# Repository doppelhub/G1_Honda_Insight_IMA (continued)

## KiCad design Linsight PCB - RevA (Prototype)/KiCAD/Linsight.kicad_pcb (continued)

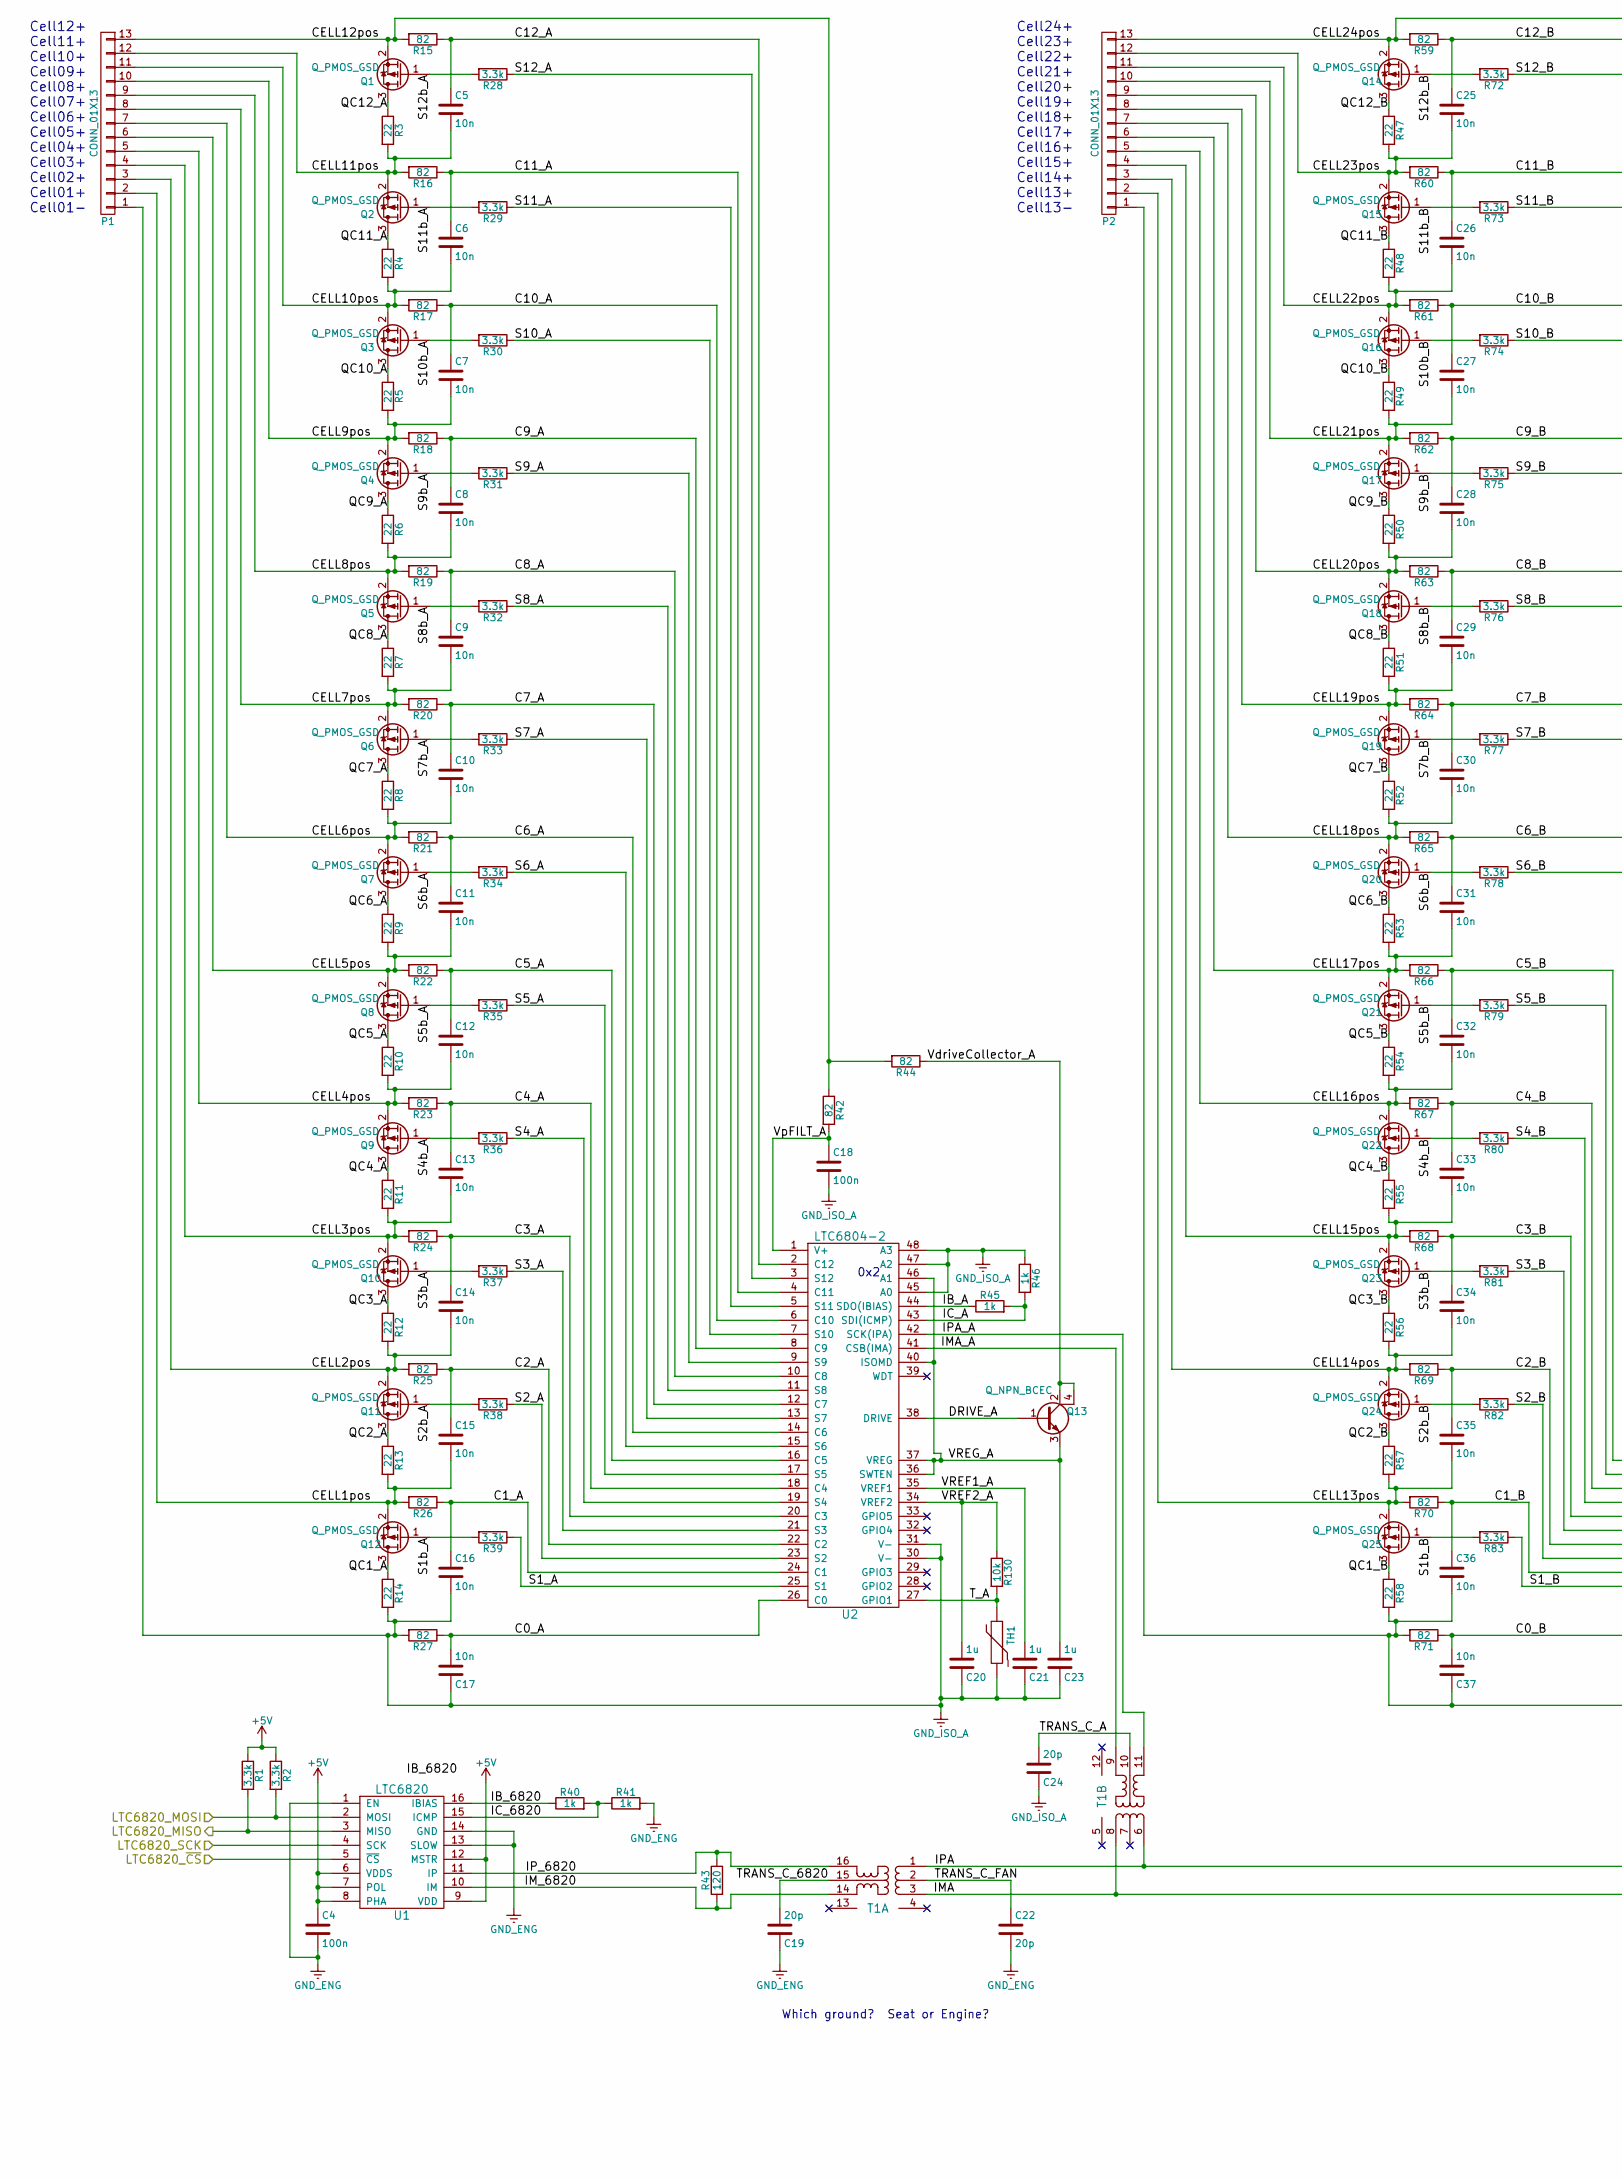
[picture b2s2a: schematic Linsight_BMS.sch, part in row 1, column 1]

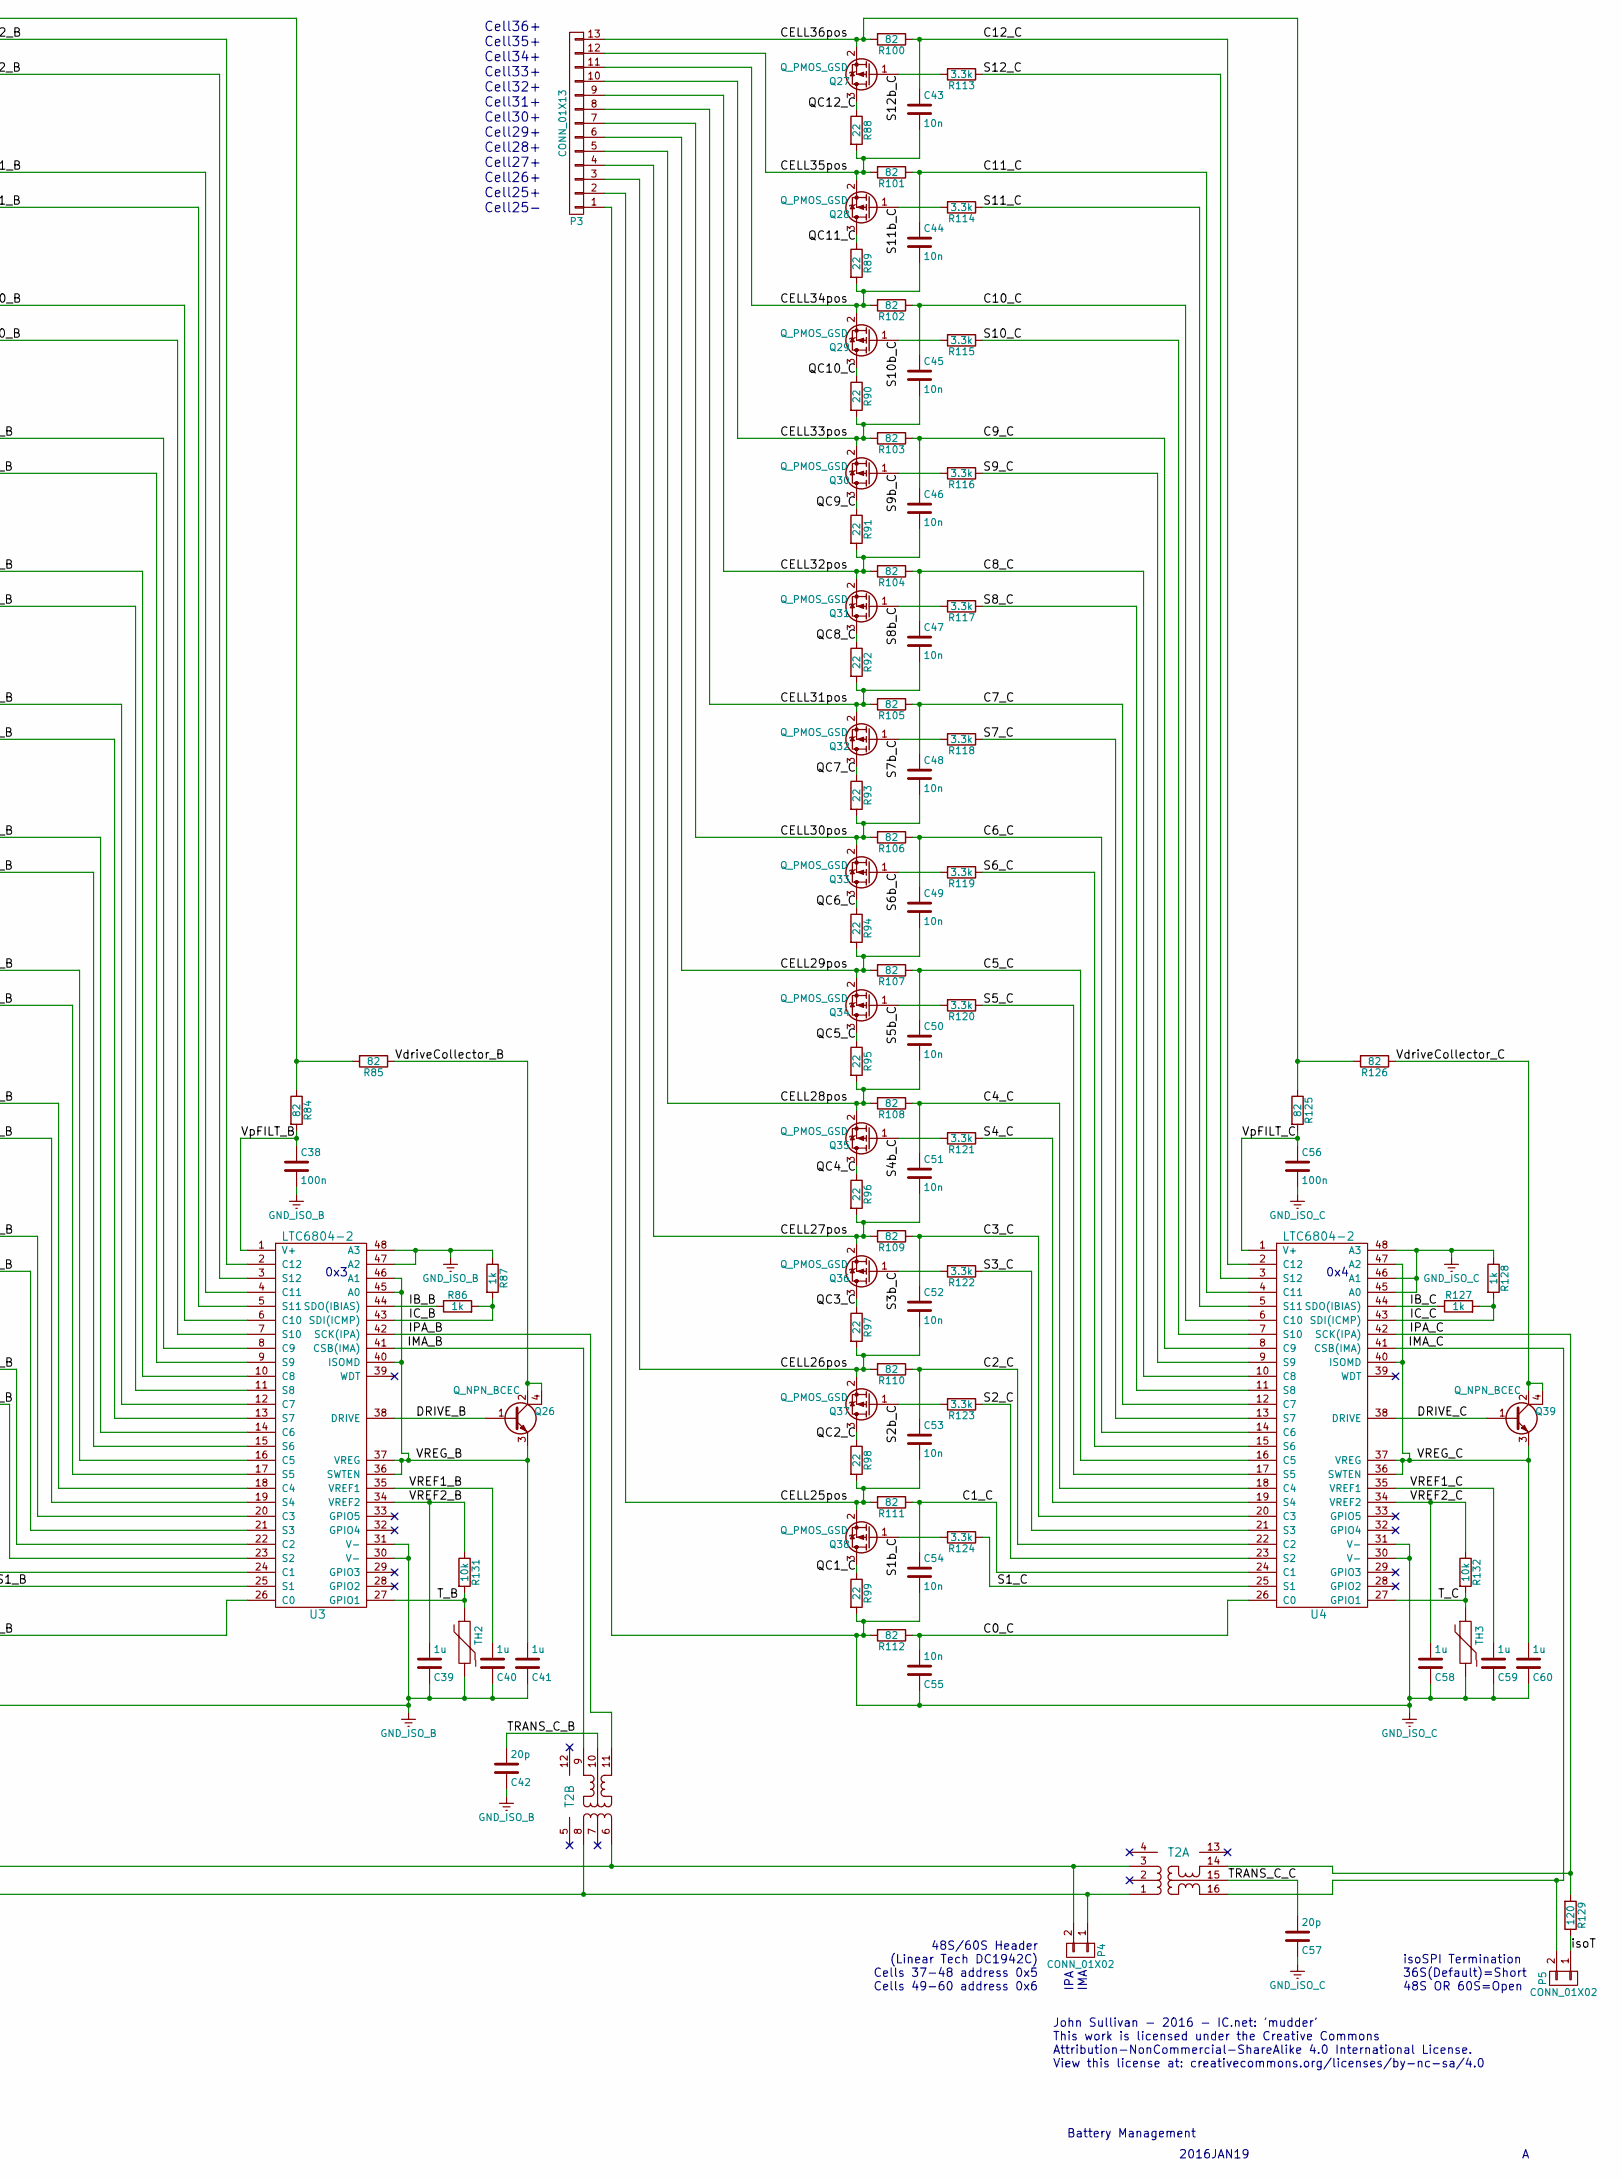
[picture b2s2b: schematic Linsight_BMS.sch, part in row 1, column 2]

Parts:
C4, C18, C38, C56: 100n; C_0805
C5, C6, C7, C8, C9, C10, C11, C12, C13, C14, C15, C16, C17, C25, C26, C27, C28, C29, C30, C31, C32, C33, C34, C35, C36, C37, C43, C44, C45, C46, C47, C48, C49, C50, C51, C52, C53, C54, C55: 10n; C_0805
C19, C22, C24, C42, C57: 20p; C_0805
C20, C21, C23, C39, C40, C41, C58, C59, C60: 1u; C_0805
P1, P2, P3: CONN_01X13; Conn_277-1232-ND
P4: CONN_01X02; Conn_1751248
P5: CONN_01X02; Pin_Header_Straight_1x02
Q1, Q2, Q3, Q4, Q5, Q6, Q7, Q8, Q9, Q10, Q11, Q12, Q14, Q15, Q16, Q17, Q18, Q19, Q20, Q21, Q22, Q23, Q24, Q25, Q27, Q28, Q29, Q30, Q31, Q32, Q33, Q34, Q35, Q36, Q37, Q38: Q_PMOS_GSD; SOT-23; Digikey BSS308PE-H6327TR-ND
Q13, Q26, Q39: Q_NPN_BCEC; SOT-223; Digikey BCP56-16T1GOSTR-ND
R1, R2, R28, R29, R30, R31, R32, R33, R34, R35, R36, R37, R38, R39, R72, R73, R74, R75, R76, R77, R78, R79, R80, R81, R82, R83, R113, R114, R115, R116, R117, R118, R119, R120, R121, R122, R123, R124: 3.3k; R_0805
R3, R4, R5, R6, R7, R8, R9, R10, R11, R12, R13, R14, R47, R48, R49, R50, R51, R52, R53, R54, R55, R56, R57, R58, R88, R89, R90, R91, R92, R93, R94, R95, R96, R97, R98, R99: 22; R_2512
R15, R16, R17, R18, R19, R20, R21, R22, R23, R24, R25, R26, R27, R42, R44, R59, R60, R61, R62, R63, R64, R65, R66, R67, R68, R69, R70, R71, R84, R85, R100, R101, R102, R103, R104, R105, R106, R107, R108, R109, R110, R111, R112, R125, R126: 82; R_0805
R40, R41, R45, R46, R86, R87, R127, R128: 1k; R_0805
R43, R129: 120; R_0805
R130, R131, R132: 10k; R_0805
T1, T2: Trans_7490100111; Trans_7490100111A
TH1, TH2, TH3: THERMISTOR; R_0805
U1: LTC6820; LTC6820_MSOP
U2, U3, U4: LTC6804-2

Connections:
+5V: C4.1, R1.1, R2.1, U1.6 (VDDS), U1.7 (POL), U1.8 (PHA), U1.9 (VDD), U1.12 (MSTR); also elsewhere on the board
/Linsight BMS/C0_A: C17.2, R27.1, U2.26 (C0)
/Linsight BMS/C0_B: C37.2, R71.1, U3.26 (C0)
/Linsight BMS/C0_C: C55.2, R112.1, U4.26 (C0)
/Linsight BMS/C1_A: C16.1, R26.1, U2.24 (C1)
/Linsight BMS/C1_B: C36.1, R70.1, U3.24 (C1)
/Linsight BMS/C1_C: C54.1, R111.1, U4.24 (C1)
/Linsight BMS/C2_A: C15.1, R25.1, U2.22 (C2)
/Linsight BMS/C2_B: C35.1, R69.1, U3.22 (C2)
/Linsight BMS/C2_C: C53.1, R110.1, U4.22 (C2)
/Linsight BMS/C3_A: C14.1, R24.1, U2.20 (C3)
/Linsight BMS/C3_B: C34.1, R68.1, U3.20 (C3)
/Linsight BMS/C3_C: C52.1, R109.1, U4.20 (C3)
/Linsight BMS/C4_A: C13.1, R23.1, U2.18 (C4)
/Linsight BMS/C4_B: C33.1, R67.1, U3.18 (C4)
/Linsight BMS/C4_C: C51.1, R108.1, U4.18 (C4)
/Linsight BMS/C5_A: C12.1, R22.1, U2.16 (C5)
/Linsight BMS/C5_B: C32.1, R66.1, U3.16 (C5)
/Linsight BMS/C5_C: C50.1, R107.1, U4.16 (C5)
/Linsight BMS/C6_A: C11.1, R21.1, U2.14 (C6)
/Linsight BMS/C6_B: C31.1, R65.1, U3.14 (C6)
/Linsight BMS/C6_C: C49.1, R106.1, U4.14 (C6)
/Linsight BMS/C7_A: C10.1, R20.1, U2.12 (C7)
/Linsight BMS/C7_B: C30.1, R64.1, U3.12 (C7)
/Linsight BMS/C7_C: C48.1, R105.1, U4.12 (C7)
/Linsight BMS/C8_A: C9.1, R19.1, U2.10 (C8)
/Linsight BMS/C8_B: C29.1, R63.1, U3.10 (C8)
/Linsight BMS/C8_C: C47.1, R104.1, U4.10 (C8)
/Linsight BMS/C9_A: C8.1, R18.1, U2.8 (C9)
/Linsight BMS/C9_B: C28.1, R62.1, U3.8 (C9)
/Linsight BMS/C9_C: C46.1, R103.1, U4.8 (C9)
/Linsight BMS/C10_A: C7.1, R17.1, U2.6 (C10)
/Linsight BMS/C10_B: C27.1, R61.1, U3.6 (C10)
/Linsight BMS/C10_C: C45.1, R102.1, U4.6 (C10)
/Linsight BMS/C11_A: C6.1, R16.1, U2.4 (C11)
/Linsight BMS/C11_B: C26.1, R60.1, U3.4 (C11)
/Linsight BMS/C11_C: C44.1, R101.1, U4.4 (C11)
/Linsight BMS/C12_A: C5.1, R15.1, U2.2 (C12)
/Linsight BMS/C12_B: C25.1, R59.1, U3.2 (C12)
/Linsight BMS/C12_C: C43.1, R100.1, U4.2 (C12)
/Linsight BMS/CELL1pos: C15.2, P1.2, Q12.2 (S), R13.2, R26.2
/Linsight BMS/CELL2pos: C14.2, P1.3, Q11.2 (S), R12.2, R25.2
/Linsight BMS/CELL3pos: C13.2, P1.4, Q10.2 (S), R11.2, R24.2
/Linsight BMS/CELL4pos: C12.2, P1.5, Q9.2 (S), R10.2, R23.2
/Linsight BMS/CELL5pos: C11.2, P1.6, Q8.2 (S), R9.2, R22.2
/Linsight BMS/CELL6pos: C10.2, P1.7, Q7.2 (S), R8.2, R21.2
/Linsight BMS/CELL7pos: C9.2, P1.8, Q6.2 (S), R7.2, R20.2
/Linsight BMS/CELL8pos: C8.2, P1.9, Q5.2 (S), R6.2, R19.2
/Linsight BMS/CELL9pos: C7.2, P1.10, Q4.2 (S), R5.2, R18.2
/Linsight BMS/CELL10pos: C6.2, P1.11, Q3.2 (S), R4.2, R17.2
/Linsight BMS/CELL11pos: C5.2, P1.12, Q2.2 (S), R3.2, R16.2
/Linsight BMS/CELL12pos: P1.13, Q1.2 (S), R15.2, R42.1, R44.2
/Linsight BMS/CELL13pos: C35.2, P2.2, Q25.2 (S), R57.2, R70.2
/Linsight BMS/CELL14pos: C34.2, P2.3, Q24.2 (S), R56.2, R69.2
/Linsight BMS/CELL15pos: C33.2, P2.4, Q23.2 (S), R55.2, R68.2
/Linsight BMS/CELL16pos: C32.2, P2.5, Q22.2 (S), R54.2, R67.2
/Linsight BMS/CELL17pos: C31.2, P2.6, Q21.2 (S), R53.2, R66.2
/Linsight BMS/CELL18pos: C30.2, P2.7, Q20.2 (S), R52.2, R65.2
/Linsight BMS/CELL19pos: C29.2, P2.8, Q19.2 (S), R51.2, R64.2
/Linsight BMS/CELL20pos: C28.2, P2.9, Q18.2 (S), R50.2, R63.2
/Linsight BMS/CELL21pos: C27.2, P2.10, Q17.2 (S), R49.2, R62.2
/Linsight BMS/CELL22pos: C26.2, P2.11, Q16.2 (S), R48.2, R61.2
/Linsight BMS/CELL23pos: C25.2, P2.12, Q15.2 (S), R47.2, R60.2
/Linsight BMS/CELL24pos: P2.13, Q14.2 (S), R59.2, R84.1, R85.2
/Linsight BMS/CELL25pos: C53.2, P3.2, Q38.2 (S), R98.2, R111.2
/Linsight BMS/CELL26pos: C52.2, P3.3, Q37.2 (S), R97.2, R110.2
/Linsight BMS/CELL27pos: C51.2, P3.4, Q36.2 (S), R96.2, R109.2
/Linsight BMS/CELL28pos: C50.2, P3.5, Q35.2 (S), R95.2, R108.2
/Linsight BMS/CELL29pos: C49.2, P3.6, Q34.2 (S), R94.2, R107.2
/Linsight BMS/CELL30pos: C48.2, P3.7, Q33.2 (S), R93.2, R106.2
/Linsight BMS/CELL31pos: C47.2, P3.8, Q32.2 (S), R92.2, R105.2
/Linsight BMS/CELL32pos: C46.2, P3.9, Q31.2 (S), R91.2, R104.2
/Linsight BMS/CELL33pos: C45.2, P3.10, Q30.2 (S), R90.2, R103.2
/Linsight BMS/CELL34pos: C44.2, P3.11, Q29.2 (S), R89.2, R102.2
/Linsight BMS/CELL35pos: C43.2, P3.12, Q28.2 (S), R88.2, R101.2
/Linsight BMS/CELL36pos: P3.13, Q27.2 (S), R100.2, R125.1, R126.2
/Linsight BMS/DRIVE_A: Q13.1 (B), U2.38 (DRIVE)
/Linsight BMS/DRIVE_B: Q26.1 (B), U3.38 (DRIVE)
/Linsight BMS/DRIVE_C: Q39.1 (B), U4.38 (DRIVE)
/Linsight BMS/IB_6820: R40.1, U1.16 (IBIAS)
/Linsight BMS/IB_A: R45.1, U2.44 (SDO(IBIAS))
/Linsight BMS/IB_B: R86.1, U3.44 (SDO(IBIAS))
/Linsight BMS/IB_C: R127.1, U4.44 (SDO(IBIAS))
/Linsight BMS/IC_6820: R40.2, R41.1, U1.15 (ICMP)
/Linsight BMS/IC_A: R45.2, R46.2, U2.43 (SDI(ICMP))
/Linsight BMS/IC_B: R86.2, R87.2, U3.43 (SDI(ICMP))
/Linsight BMS/IC_C: R127.2, R128.2, U4.43 (SDI(ICMP))
/Linsight BMS/IMA: P4.1, T1.3, T1.8, T2.1, T2.8
/Linsight BMS/IMA_A: T1.9, U2.41 (CSB(IMA))
/Linsight BMS/IMA_B: T2.9, U3.41 (CSB(IMA))
/Linsight BMS/IMA_C: P5.2, T2.16, U4.41 (CSB(IMA))
/Linsight BMS/IM_6820: R43.2, T1.14, U1.10 (IM)
/Linsight BMS/IPA: P4.2, T1.1, T1.6, T2.3, T2.6
/Linsight BMS/IPA_A: T1.11, U2.42 (SCK(IPA))
/Linsight BMS/IPA_B: T2.11, U3.42 (SCK(IPA))
/Linsight BMS/IPA_C: R129.2, T2.14, U4.42 (SCK(IPA))
/Linsight BMS/IP_6820: R43.1, T1.16, U1.11 (IP)
/Linsight BMS/LTC6820_MISO: R1.2, U1.3 (MISO); also elsewhere on the board
/Linsight BMS/LTC6820_MOSI: R2.2, U1.2 (MOSI); also elsewhere on the board
/Linsight BMS/LTC6820_SCK: U1.4 (SCK); also elsewhere on the board
/Linsight BMS/LTC6820_~CS: U1.5 (~CS); also elsewhere on the board
/Linsight BMS/QC1_A: Q12.3 (D), R14.1
/Linsight BMS/QC1_B: Q25.3 (D), R58.1
/Linsight BMS/QC1_C: Q38.3 (D), R99.1
/Linsight BMS/QC2_A: Q11.3 (D), R13.1
/Linsight BMS/QC2_B: Q24.3 (D), R57.1
/Linsight BMS/QC2_C: Q37.3 (D), R98.1
/Linsight BMS/QC3_A: Q10.3 (D), R12.1
/Linsight BMS/QC3_B: Q23.3 (D), R56.1
/Linsight BMS/QC3_C: Q36.3 (D), R97.1
/Linsight BMS/QC4_A: Q9.3 (D), R11.1
/Linsight BMS/QC4_B: Q22.3 (D), R55.1
/Linsight BMS/QC4_C: Q35.3 (D), R96.1
/Linsight BMS/QC5_A: Q8.3 (D), R10.1
/Linsight BMS/QC5_B: Q21.3 (D), R54.1
/Linsight BMS/QC5_C: Q34.3 (D), R95.1
/Linsight BMS/QC6_A: Q7.3 (D), R9.1
/Linsight BMS/QC6_B: Q20.3 (D), R53.1
/Linsight BMS/QC6_C: Q33.3 (D), R94.1
/Linsight BMS/QC7_A: Q6.3 (D), R8.1
/Linsight BMS/QC7_B: Q19.3 (D), R52.1
/Linsight BMS/QC7_C: Q32.3 (D), R93.1
/Linsight BMS/QC8_A: Q5.3 (D), R7.1
/Linsight BMS/QC8_B: Q18.3 (D), R51.1
/Linsight BMS/QC8_C: Q31.3 (D), R92.1
/Linsight BMS/QC9_A: Q4.3 (D), R6.1
/Linsight BMS/QC9_B: Q17.3 (D), R50.1
/Linsight BMS/QC9_C: Q30.3 (D), R91.1
/Linsight BMS/QC10_A: Q3.3 (D), R5.1
/Linsight BMS/QC10_B: Q16.3 (D), R49.1
/Linsight BMS/QC10_C: Q29.3 (D), R90.1
/Linsight BMS/QC11_A: Q2.3 (D), R4.1
/Linsight BMS/QC11_B: Q15.3 (D), R48.1
/Linsight BMS/QC11_C: Q28.3 (D), R89.1
/Linsight BMS/QC12_A: Q1.3 (D), R3.1
/Linsight BMS/QC12_B: Q14.3 (D), R47.1
/Linsight BMS/QC12_C: Q27.3 (D), R88.1
/Linsight BMS/S1_A: R39.1, U2.25 (S1)
/Linsight BMS/S1_B: R83.1, U3.25 (S1)
/Linsight BMS/S1_C: R124.1, U4.25 (S1)
/Linsight BMS/S1b_A: Q12.1 (G), R39.2
/Linsight BMS/S1b_B: Q25.1 (G), R83.2
/Linsight BMS/S1b_C: Q38.1 (G), R124.2
/Linsight BMS/S2_A: R38.1, U2.23 (S2)
/Linsight BMS/S2_B: R82.1, U3.23 (S2)
/Linsight BMS/S2_C: R123.1, U4.23 (S2)
/Linsight BMS/S2b_A: Q11.1 (G), R38.2
/Linsight BMS/S2b_B: Q24.1 (G), R82.2
/Linsight BMS/S2b_C: Q37.1 (G), R123.2
/Linsight BMS/S3_A: R37.1, U2.21 (S3)
/Linsight BMS/S3_B: R81.1, U3.21 (S3)
/Linsight BMS/S3_C: R122.1, U4.21 (S3)
/Linsight BMS/S3b_A: Q10.1 (G), R37.2
/Linsight BMS/S3b_B: Q23.1 (G), R81.2
/Linsight BMS/S3b_C: Q36.1 (G), R122.2
/Linsight BMS/S4_A: R36.1, U2.19 (S4)
/Linsight BMS/S4_B: R80.1, U3.19 (S4)
/Linsight BMS/S4_C: R121.1, U4.19 (S4)
/Linsight BMS/S4b_A: Q9.1 (G), R36.2
/Linsight BMS/S4b_B: Q22.1 (G), R80.2
/Linsight BMS/S4b_C: Q35.1 (G), R121.2
/Linsight BMS/S5_A: R35.1, U2.17 (S5)
/Linsight BMS/S5_B: R79.1, U3.17 (S5)
/Linsight BMS/S5_C: R120.1, U4.17 (S5)
/Linsight BMS/S5b_A: Q8.1 (G), R35.2
/Linsight BMS/S5b_B: Q21.1 (G), R79.2
/Linsight BMS/S5b_C: Q34.1 (G), R120.2
/Linsight BMS/S6_A: R34.1, U2.15 (S6)
/Linsight BMS/S6_B: R78.1, U3.15 (S6)
/Linsight BMS/S6_C: R119.1, U4.15 (S6)
/Linsight BMS/S6b_A: Q7.1 (G), R34.2
/Linsight BMS/S6b_B: Q20.1 (G), R78.2
/Linsight BMS/S6b_C: Q33.1 (G), R119.2
/Linsight BMS/S7_A: R33.1, U2.13 (S7)
/Linsight BMS/S7_B: R77.1, U3.13 (S7)
/Linsight BMS/S7_C: R118.1, U4.13 (S7)
/Linsight BMS/S7b_A: Q6.1 (G), R33.2
/Linsight BMS/S7b_B: Q19.1 (G), R77.2
/Linsight BMS/S7b_C: Q32.1 (G), R118.2
/Linsight BMS/S8_A: R32.1, U2.11 (S8)
/Linsight BMS/S8_B: R76.1, U3.11 (S8)
/Linsight BMS/S8_C: R117.1, U4.11 (S8)
/Linsight BMS/S8b_A: Q5.1 (G), R32.2
/Linsight BMS/S8b_B: Q18.1 (G), R76.2
/Linsight BMS/S8b_C: Q31.1 (G), R117.2
/Linsight BMS/S9_A: R31.1, U2.9 (S9)
/Linsight BMS/S9_B: R75.1, U3.9 (S9)
/Linsight BMS/S9_C: R116.1, U4.9 (S9)
/Linsight BMS/S9b_A: Q4.1 (G), R31.2
/Linsight BMS/S9b_B: Q17.1 (G), R75.2
/Linsight BMS/S9b_C: Q30.1 (G), R116.2
/Linsight BMS/S10_A: R30.1, U2.7 (S10)
/Linsight BMS/S10_B: R74.1, U3.7 (S10)
/Linsight BMS/S10_C: R115.1, U4.7 (S10)
/Linsight BMS/S10b_A: Q3.1 (G), R30.2
/Linsight BMS/S10b_B: Q16.1 (G), R74.2
/Linsight BMS/S10b_C: Q29.1 (G), R115.2
/Linsight BMS/S11_A: R29.1, U2.5 (S11)
/Linsight BMS/S11_B: R73.1, U3.5 (S11)
/Linsight BMS/S11_C: R114.1, U4.5 (S11)
/Linsight BMS/S11b_A: Q2.1 (G), R29.2
/Linsight BMS/S11b_B: Q15.1 (G), R73.2
/Linsight BMS/S11b_C: Q28.1 (G), R114.2
/Linsight BMS/S12_A: R28.1, U2.3 (S12)
/Linsight BMS/S12_B: R72.1, U3.3 (S12)
/Linsight BMS/S12_C: R113.1, U4.3 (S12)
/Linsight BMS/S12b_A: Q1.1 (G), R28.2
/Linsight BMS/S12b_B: Q14.1 (G), R72.2
/Linsight BMS/S12b_C: Q27.1 (G), R113.2
/Linsight BMS/TRANS_C_6820: C19.2, T1.15
/Linsight BMS/TRANS_C_A: C24.2, T1.10
/Linsight BMS/TRANS_C_B: C42.2, T2.10
/Linsight BMS/TRANS_C_C: C57.2, T2.15
/Linsight BMS/TRANS_C_FAN: C22.1, T1.2
/Linsight BMS/T_A: R130.2, TH1.1, U2.27 (GPIO1)
/Linsight BMS/T_B: R131.2, TH2.1, U3.27 (GPIO1)
/Linsight BMS/T_C: R132.2, TH3.1, U4.27 (GPIO1)
/Linsight BMS/VREF1_A: C21.2, U2.35 (VREF1)
/Linsight BMS/VREF1_B: C40.2, U3.35 (VREF1)
/Linsight BMS/VREF1_C: C59.2, U4.35 (VREF1)
/Linsight BMS/VREF2_A: C20.2, R130.1, U2.34 (VREF2)
/Linsight BMS/VREF2_B: C39.2, R131.1, U3.34 (VREF2)
/Linsight BMS/VREF2_C: C58.2, R132.1, U4.34 (VREF2)
/Linsight BMS/VREG_A: C23.2, Q13.3 (E), U2.36 (SWTEN), U2.37 (VREG), U2.40 (ISOMD), U2.46 (A1)
/Linsight BMS/VREG_B: C41.2, Q26.3 (E), U3.36 (SWTEN), U3.37 (VREG), U3.40 (ISOMD), U3.45 (A0), U3.46 (A1)
/Linsight BMS/VREG_C: C60.2, Q39.3 (E), U4.36 (SWTEN), U4.37 (VREG), U4.40 (ISOMD), U4.47 (A2)
/Linsight BMS/VdriveCollector_A: Q13.2 (C), Q13.4 (C), R44.1
/Linsight BMS/VdriveCollector_B: Q26.2 (C), Q26.4 (C), R85.1
/Linsight BMS/VdriveCollector_C: Q39.2 (C), Q39.4 (C), R126.1
/Linsight BMS/VpFILT_A: C18.1, R42.2, U2.1 (V+)
/Linsight BMS/VpFILT_B: C38.1, R84.2, U3.1 (V+)
/Linsight BMS/VpFILT_C: C56.1, R125.2, U4.1 (V+)
/Linsight BMS/isoT: P5.1, R129.1
GND_ENG: C4.2, C19.1, C22.2, R41.2, U1.1 (EN), U1.13 (SLOW), U1.14 (GND); also elsewhere on the board
GND_ISO_A: C16.2, C17.1, C18.2, C20.1, C21.1, C23.1, C24.1, P1.1, R14.2, R27.2, R46.1, TH1.2, U2.30 (V-), U2.31 (V-), U2.45 (A0), U2.47 (A2), U2.48 (A3)
GND_ISO_B: C36.2, C37.1, C38.2, C39.1, C40.1, C41.1, C42.1, P2.1, R58.2, R71.2, R87.1, TH2.2, U3.30 (V-), U3.31 (V-), U3.47 (A2), U3.48 (A3)
GND_ISO_C: C54.2, C55.1, C56.2, C57.1, C58.1, C59.1, C60.1, P3.1, R99.2, R112.2, R128.1, TH3.2, U4.30 (V-), U4.31 (V-), U4.45 (A0), U4.46 (A1), U4.48 (A3)

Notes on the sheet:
0x2
0x3
0x4
isoSPI Termination 36S(Default)=Short 48S OR 60S=Open
Cell12+ Cell11+ Cell10+ Cell09+ Cell08+ Cell07+ Cell06+ Cell05+ Cell04+ Cell03+ Cell02+ Cell01+ Cell01-
Cell24+ Cell23+ Cell22+ Cell21+ Cell20+ Cell19+ Cell18+ Cell17+ Cell16+ Cell15+ Cell14+ Cell13+ Cell13-
Cell36+ Cell35+ Cell34+ Cell33+ Cell32+ Cell31+ Cell30+ Cell29+ Cell28+ Cell27+ Cell26+ Cell25+ Cell25-
48S/60S Header (Linear Tech DC1942C) Cells 37-48 address 0x5 Cells 49-60 address 0x6
IPA IMA
Which ground? Seat or Engine?
John Sullivan - 2016 - IC.net: 'mudder' This work is licensed under the Creative Commons Attribution-NonCommercial-ShareAlike 4.0 International License. View this license at: creativecommons.org/licenses/by-nc-sa/4.0
Battery Management
2016JAN19

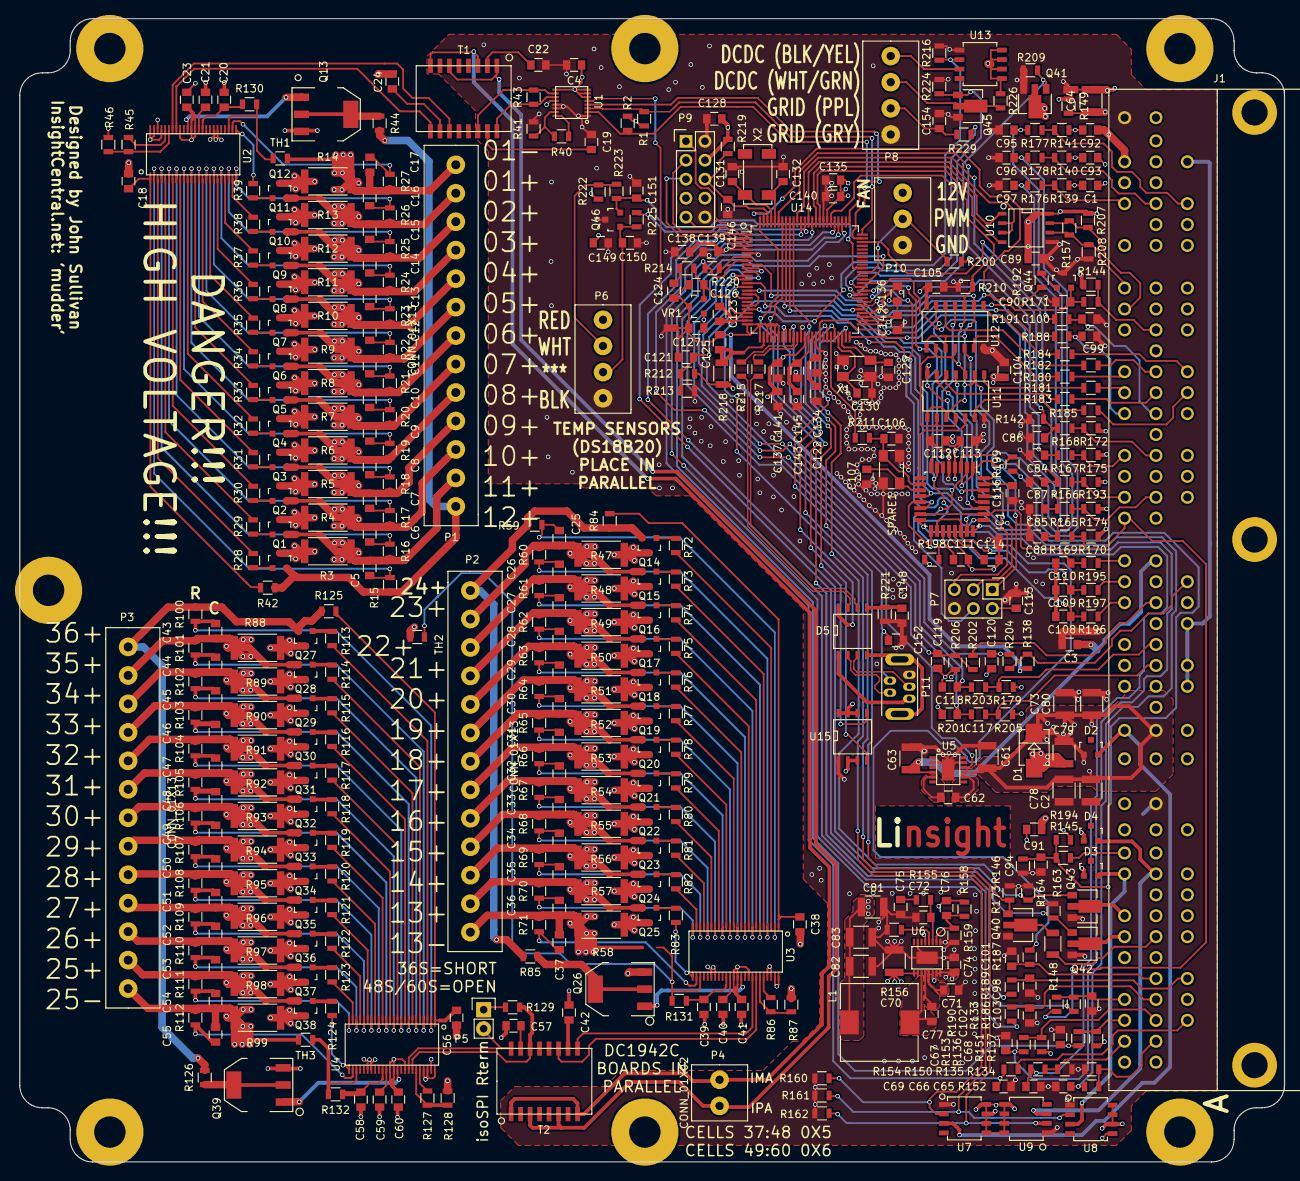
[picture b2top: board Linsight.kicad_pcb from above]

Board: 4 copper layers, 169.2 x 153.0 mm, 474 parts (0 on the bottom side), 404 nets.

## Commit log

2020-04-21 Create .gitignore
    For .DS_Store
2020-07-02 Added general overview image
2020-07-02 Inverted schematic
    Makes it easier for people to understand.
2020-10-29 Clarified HVDC bus in Schematic
    Per feedback from ic.net user *sean*, I clarified how the HVDC bus routes through the IMA system; I bolded this path, and graphically changed the layout. I also noted that there is no DC path from HV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
2020-10-29 Changed revision date
2023-07-20 Removed Extra Files
2023-08-06 Notes to IMA Bay Wiring
2024-09-07 Added fan power & resistor values
2025-11-06 Schematic Update
2026-05-30 DCDC Input Fuse and Hall Sensor Tester
2026-05-31 Set initial hallState to static variable
2026-05-31 Narrow wrap around logic
2026-05-31 Added E-tachometer debug text
2026-05-31 Updated instructions
